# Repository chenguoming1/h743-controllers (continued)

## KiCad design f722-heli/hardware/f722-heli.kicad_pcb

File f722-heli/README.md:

# F722 controller: native0 routed milestone, work in progress

**Open [hardware/f722-heli.kicad_pro](hardware/f722-heli.kicad_pro). The selected board has zero opens, geometric DRC errors, DRC warnings, ERC findings and parity findings. It is a fully routed geometric WIP milestone; fresh conditional DC is now recorded in the evidence supplement; electrical-system acceptance and manufacturing/flight qualification remain pending.**

PCB SHA-256: `84229c571433bd72d410fb18d02cffa3a380c00a87fbe1270e3a73b63f8dd6cd`. The [native0 checkpoint](layout-revision/checkpoints/native0-rx-complete-v1-20261013/README.md) and [canonical provenance](hardware/CANONICAL-SOURCE.json) bind all 61 paired design files. Only the PCB differs from native1; all 60 non-PCB files are exact.

The cumulative native change removes 18 tracks and one via, adds 36 tracks and two vias, and moves U15, R34 and R35 through three measured cardinal transforms, preserving all pad-net mappings. It has 2,525 native objects and 331 drilled objects. The separate final GREEN cleanup removes two exact remnants. All required new physical gates and all 22 actual IO protection checks pass. Scoped cleanup reference applicability and residual RX crossing/MISO edge concerns are recorded in the checkpoint; geometry checks do not establish fast-edge or ESD equivalence.

The fresh selected-source DC result passes **294 required accessory/logic/USB cases on both grids**, 15 numerical comparisons and five VCAP copper loops. All 11 servo cases are illustrations. Six heavier current illustrations exceed the version-qualified Hobbywing V4.1 **10 A continuous BEC** reference even where ideal-source board-pad voltage passes. The raw aggregate remains false for the 18.56 A single-feed illustration, whose four servo pads fall below 6 V. This result does not qualify the servo system. The intended KST servos specify **6.0-8.4 V; raw 12.6 V servo operation is excluded**. The raw servo bus bypasses U5 electronics protection. V4.1's 30 A peak figure provides no installed duty-cycle qualification, and actual ESC/servo revisions, mating contacts and harness limits remain unbound. See the [power scope correction](layout-revision/checkpoints/native0-rx-complete-v1-20261013/evidence/power/POWER-SCOPE-CORRECTION.md).

The conditional 27 MHz prototype/bench limits, flash settling, BARO/IMU noise and ESD/EMC checks remain. The approved requested 400 kHz I2C setup remains unapplied; it can produce an actual bus clock above 400 kHz under the reviewed timing assumptions. The 385 kHz refinement remains unapproved and unapplied. Both new signal vias retain exact tenting/mask and actual pad/paste/metal-clearance evidence, including GREEN in the flash package region. JLC filled/capped-process applicability, ordinary-via process/stack, USB slots and panel acceptance remain unresolved. No process or firmware change is made here.

Saved-board restoration from the public native1 source is tested byte-for-byte. The compact cumulative transaction data and original two-stage native evidence are preserved; a full portable native-proof replay is not claimed. No heavy native, geometry or solver workload was repeated for packaging. The [conditional DC and local assembly supplement](layout-revision/checkpoints/native0-rx-complete-v1-20261013/supplements/conditional-dc-v1/README.md) records fresh native0 evidence and complete reduced results. The full raw field archive remains local with exact hashes; portable heavy replay is unrun. The nominal moved-part review passes while factory process acceptance remains open. Native1 results remain historical.

The [static firmware mapping receipt](layout-revision/checkpoints/native0-rx-complete-v1-20261013/supplements/conditional-dc-v1/firmware/REVIEW.md) passes 29 mapping rows and enumerates all 31 target resources, including shared PPM/SBUS and unused TX1. Installed binary, boot/DFU, IMU axes and physical runtime remain unverified.

The [static IMU and internal CAM supplement](layout-revision/checkpoints/native0-rx-complete-v1-20261013/supplements/imu-cam-v1/README.md) records the A/B-edge-forward orientation, actual INTERNAL WIP outputs, the drill-comparison tool correction and preserved U15 mask-contour differences. [Remaining decisions and acceptance gates](layout-revision/checkpoints/native0-rx-complete-v1-20261013/supplements/imu-cam-v1/OUTSTANDING-GATES.md) separate system choices, factory acceptance and prototype tests.

## Historical manufacturing records

Older docs/, validation/, manufacturing/ exports and [final95 status](README-final95-historical.md) describe earlier geometry. Regenerate final assembly outputs from the eventual released board and verify factory orientation. Selected R35 is at (29.2,23.9), B.Cu, 180 degrees; the historical native1 270-degree note is inapplicable. U15 and R34 also use their selected measured poses. All prior checkpoints and B-RID files remain unchanged. See [layout history](layout-revision/README.md). No fabrication or flight release is made here.

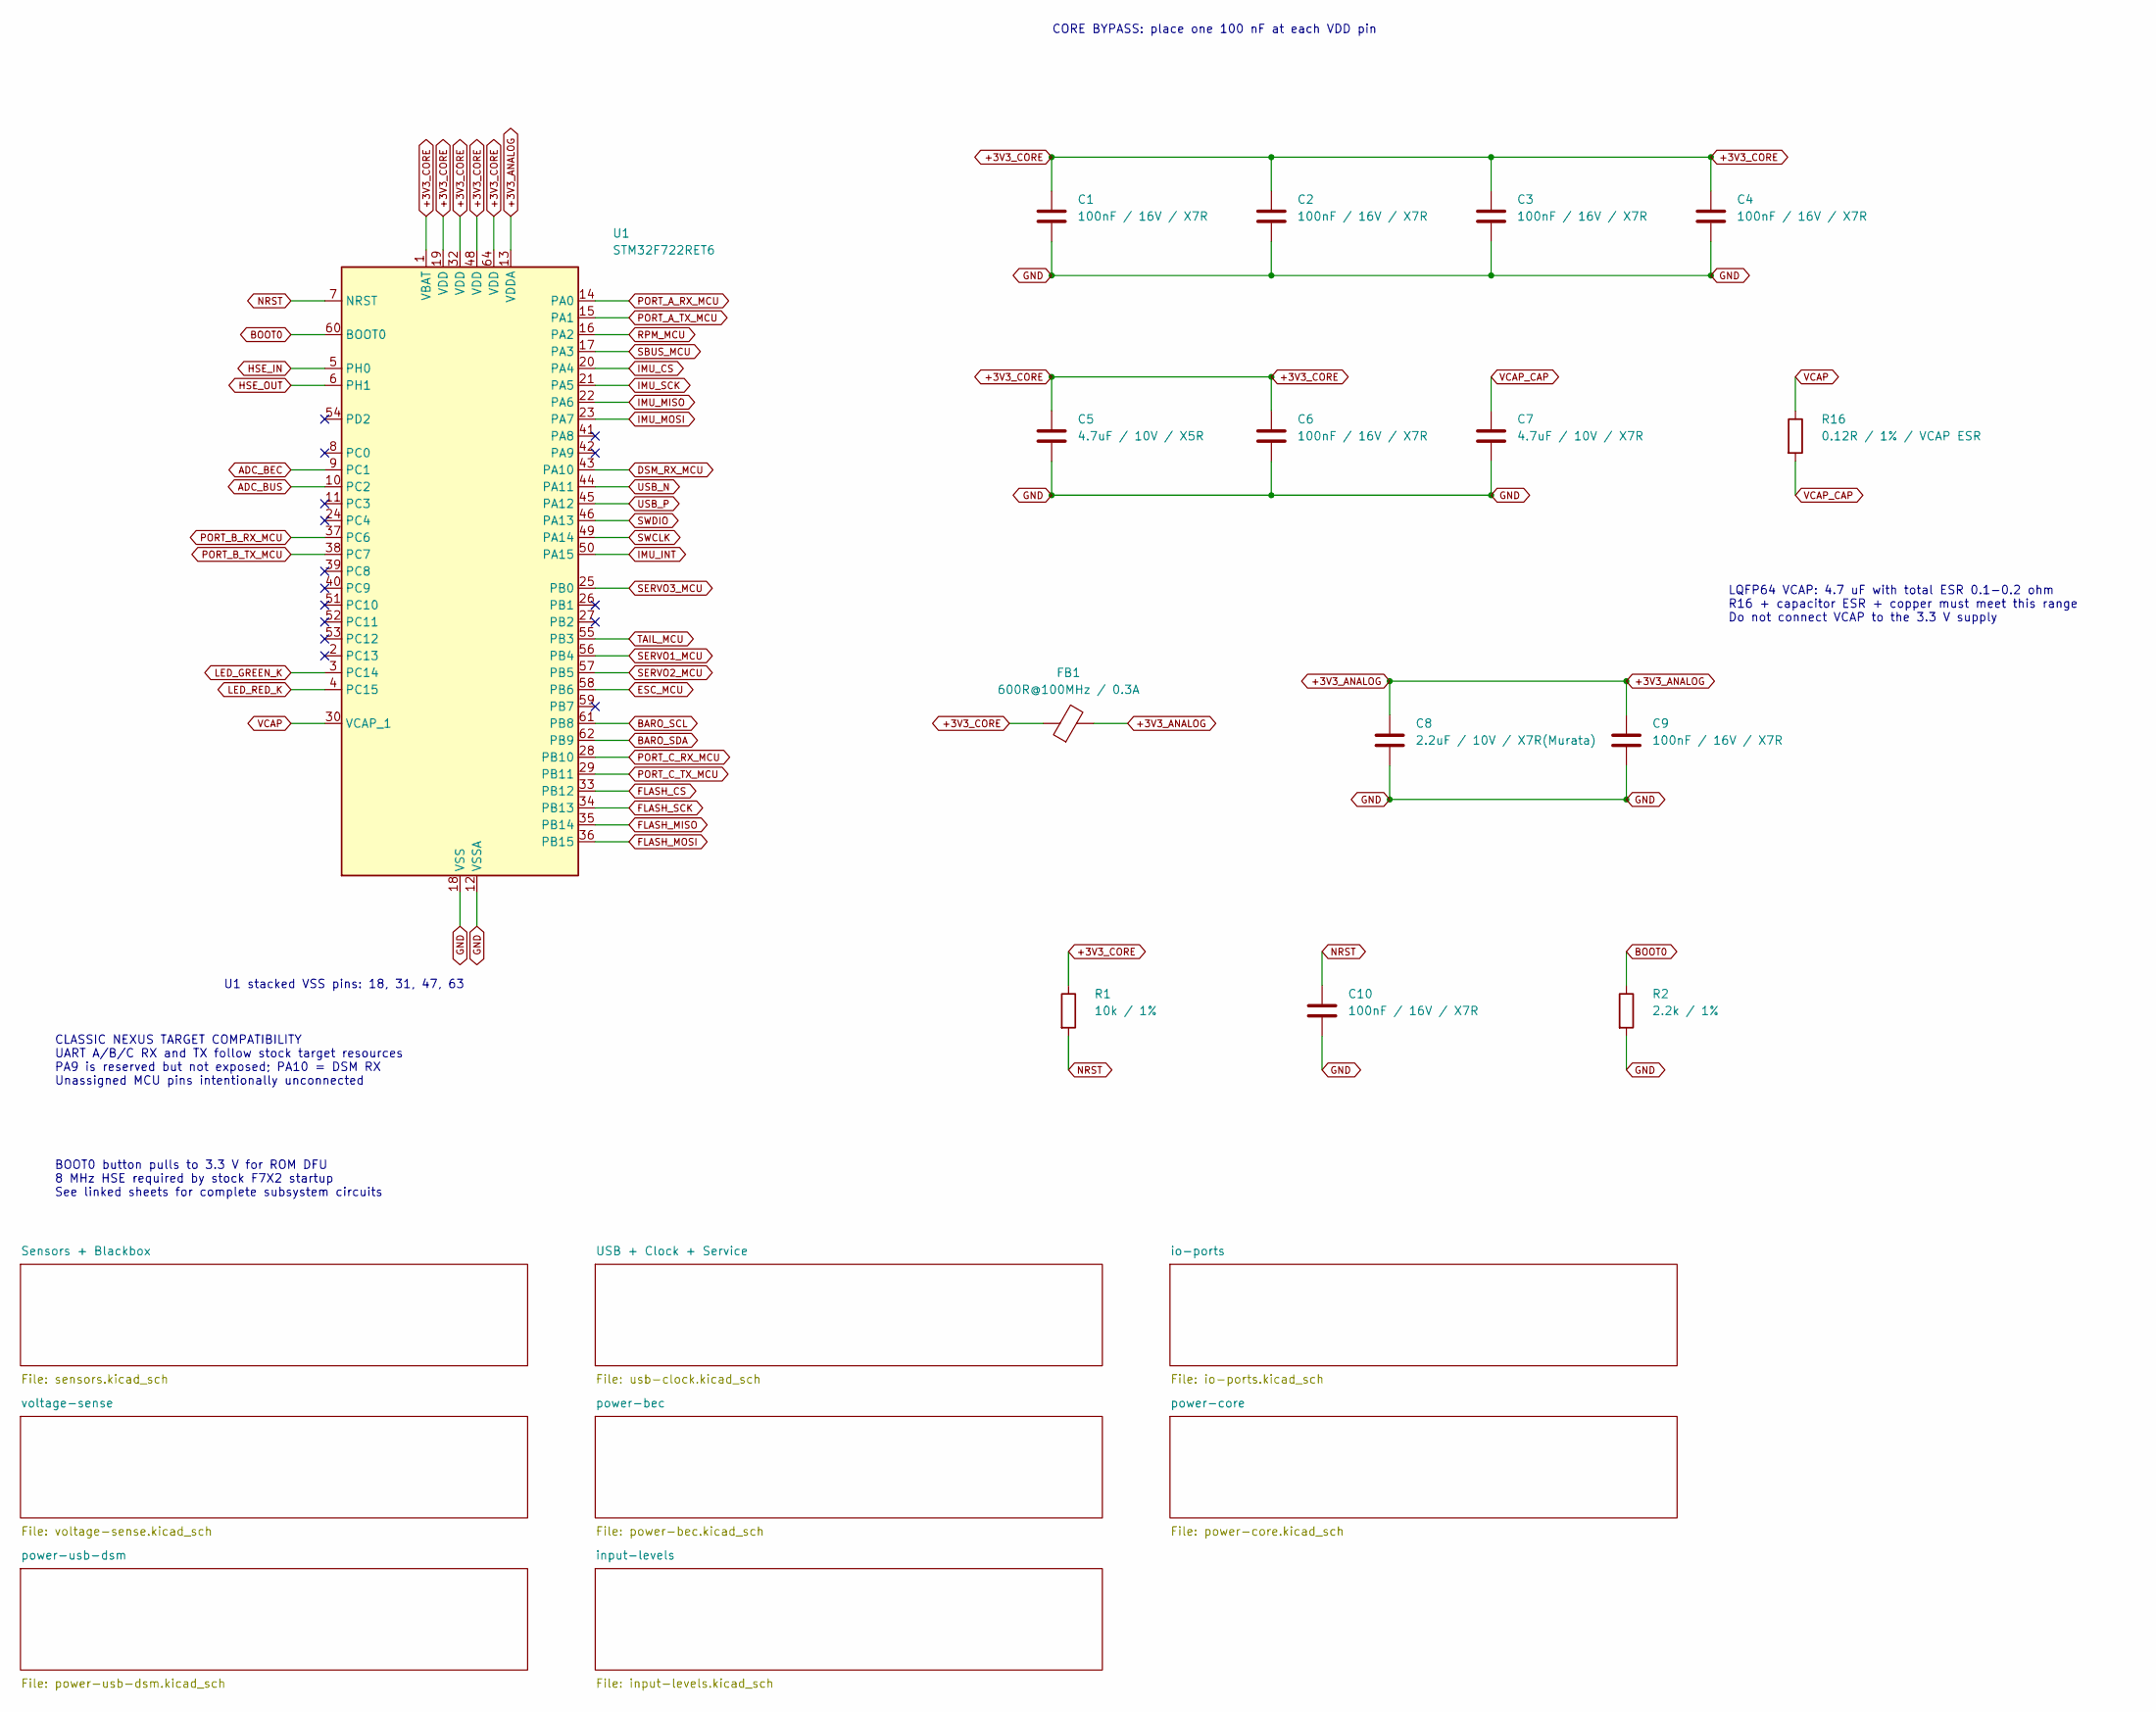
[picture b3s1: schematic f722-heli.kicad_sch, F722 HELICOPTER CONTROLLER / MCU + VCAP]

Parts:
C1, C2, C3, C4, C6, C9, C10: 100nF / 16V / X7R; C_0402_1005Metric; MPN CL05B104KO5NNNC; LCSC C1525
C5: 4.7uF / 10V / X5R; C_0603_1608Metric; MPN CL10A475KP8NNNC; LCSC C1705
C7: 4.7uF / 10V / X7R; C_0603_1608Metric; MPN GRM188Z71A475KE15D; LCSC C913474
C8: 2.2uF / 10V / X7R(Murata); Murata_GRM155Z71A225KE44_0402; MPN GRM155Z71A225KE44D; LCSC C2999759
FB1: 600R@100MHz / 0.3A; Murata_BLM15AG_0402; MPN BLM15AG601SN1D; LCSC C76884
R1: 10k / 1%; R_0402_1005Metric; MPN 0402WGF1002TCE; LCSC C25744
R2: 2.2k / 1%; R_0402_1005Metric; MPN 0402WGF2201TCE; LCSC C25879
R16: 0.12R / 1% / VCAP ESR; R_Panasonic_ERJ3R_0603; MPN ERJ3RSFR12V; LCSC C4059772
U1: STM32F722RET6; LQFP-64_10x10mm_P0.5mm; MPN STM32F722RET6; LCSC C118207

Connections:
+3V3_ANALOG: C8.1, C9.1, FB1.2, U1.13 (VDDA)
+3V3_CORE: C1.1, C2.1, C3.1, C4.1, C5.1, C6.1, FB1.1, R1.1, U1.1 (VBAT), U1.19 (VDD), U1.32 (VDD), U1.48 (VDD), U1.64 (VDD); also elsewhere on the board
ADC_BEC: U1.9 (PC1); also elsewhere on the board
ADC_BUS: U1.10 (PC2); also elsewhere on the board
BARO_SCL: U1.61 (PB8); also elsewhere on the board
BARO_SDA: U1.62 (PB9); also elsewhere on the board
BOOT0: R2.1, U1.60 (BOOT0); also elsewhere on the board
DSM_RX_MCU: U1.43 (PA10); also elsewhere on the board
FLASH_CS: U1.33 (PB12); also elsewhere on the board
FLASH_MISO: U1.35 (PB14); also elsewhere on the board
FLASH_MOSI: U1.36 (PB15); also elsewhere on the board
FLASH_SCK: U1.34 (PB13); also elsewhere on the board
GND: C1.2, C2.2, C3.2, C4.2, C5.2, C6.2, C7.2, C8.2, C9.2, C10.2, R2.2, U1.12 (VSSA), U1.18 (VSS), U1.31 (VSS), U1.47 (VSS), U1.63 (VSS); also elsewhere on the board
HSE_IN: U1.5 (PH0); also elsewhere on the board
HSE_OUT: U1.6 (PH1); also elsewhere on the board
IMU_CS: U1.20 (PA4); also elsewhere on the board
IMU_INT: U1.50 (PA15); also elsewhere on the board
IMU_MISO: U1.22 (PA6); also elsewhere on the board
IMU_MOSI: U1.23 (PA7); also elsewhere on the board
IMU_SCK: U1.21 (PA5); also elsewhere on the board
LED_GREEN_K: U1.3 (PC14); also elsewhere on the board
LED_RED_K: U1.4 (PC15); also elsewhere on the board
NRST: C10.1, R1.2, U1.7 (NRST); also elsewhere on the board
PORT_A_RX_MCU: U1.14 (PA0); also elsewhere on the board
PORT_A_TX_MCU: U1.15 (PA1); also elsewhere on the board
PORT_B_RX_MCU: U1.37 (PC6); also elsewhere on the board
PORT_B_TX_MCU: U1.38 (PC7); also elsewhere on the board
PORT_C_RX_MCU: U1.28 (PB10); also elsewhere on the board
PORT_C_TX_MCU: U1.29 (PB11); also elsewhere on the board
SERVO1_MCU: U1.56 (PB4); also elsewhere on the board
SERVO2_MCU: U1.57 (PB5); also elsewhere on the board
SERVO3_MCU: U1.25 (PB0); also elsewhere on the board
SWCLK: U1.49 (PA14); also elsewhere on the board
SWDIO: U1.46 (PA13); also elsewhere on the board
TAIL_MCU: U1.55 (PB3); also elsewhere on the board
USB_N: U1.44 (PA11); also elsewhere on the board
USB_P: U1.45 (PA12); also elsewhere on the board
VCAP: R16.1, U1.30 (VCAP_1)
VCAP_CAP: C7.1, R16.2

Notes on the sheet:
CLASSIC NEXUS TARGET COMPATIBILITY UART A/B/C RX and TX follow stock target resources PA9 is reserved but not exposed; PA10 = DSM RX Unassigned MCU pins intentionally unconnected
CORE BYPASS: place one 100 nF at each VDD pin
LQFP64 VCAP: 4.7 uF with total ESR 0.1-0.2 ohm R16 + capacitor ESR + copper must meet this range Do not connect VCAP to the 3.3 V supply
BOOT0 button pulls to 3.3 V for ROM DFU 8 MHz HSE required by stock F7X2 startup See linked sheets for complete subsystem circuits
U1 stacked VSS pins: 18, 31, 47, 63

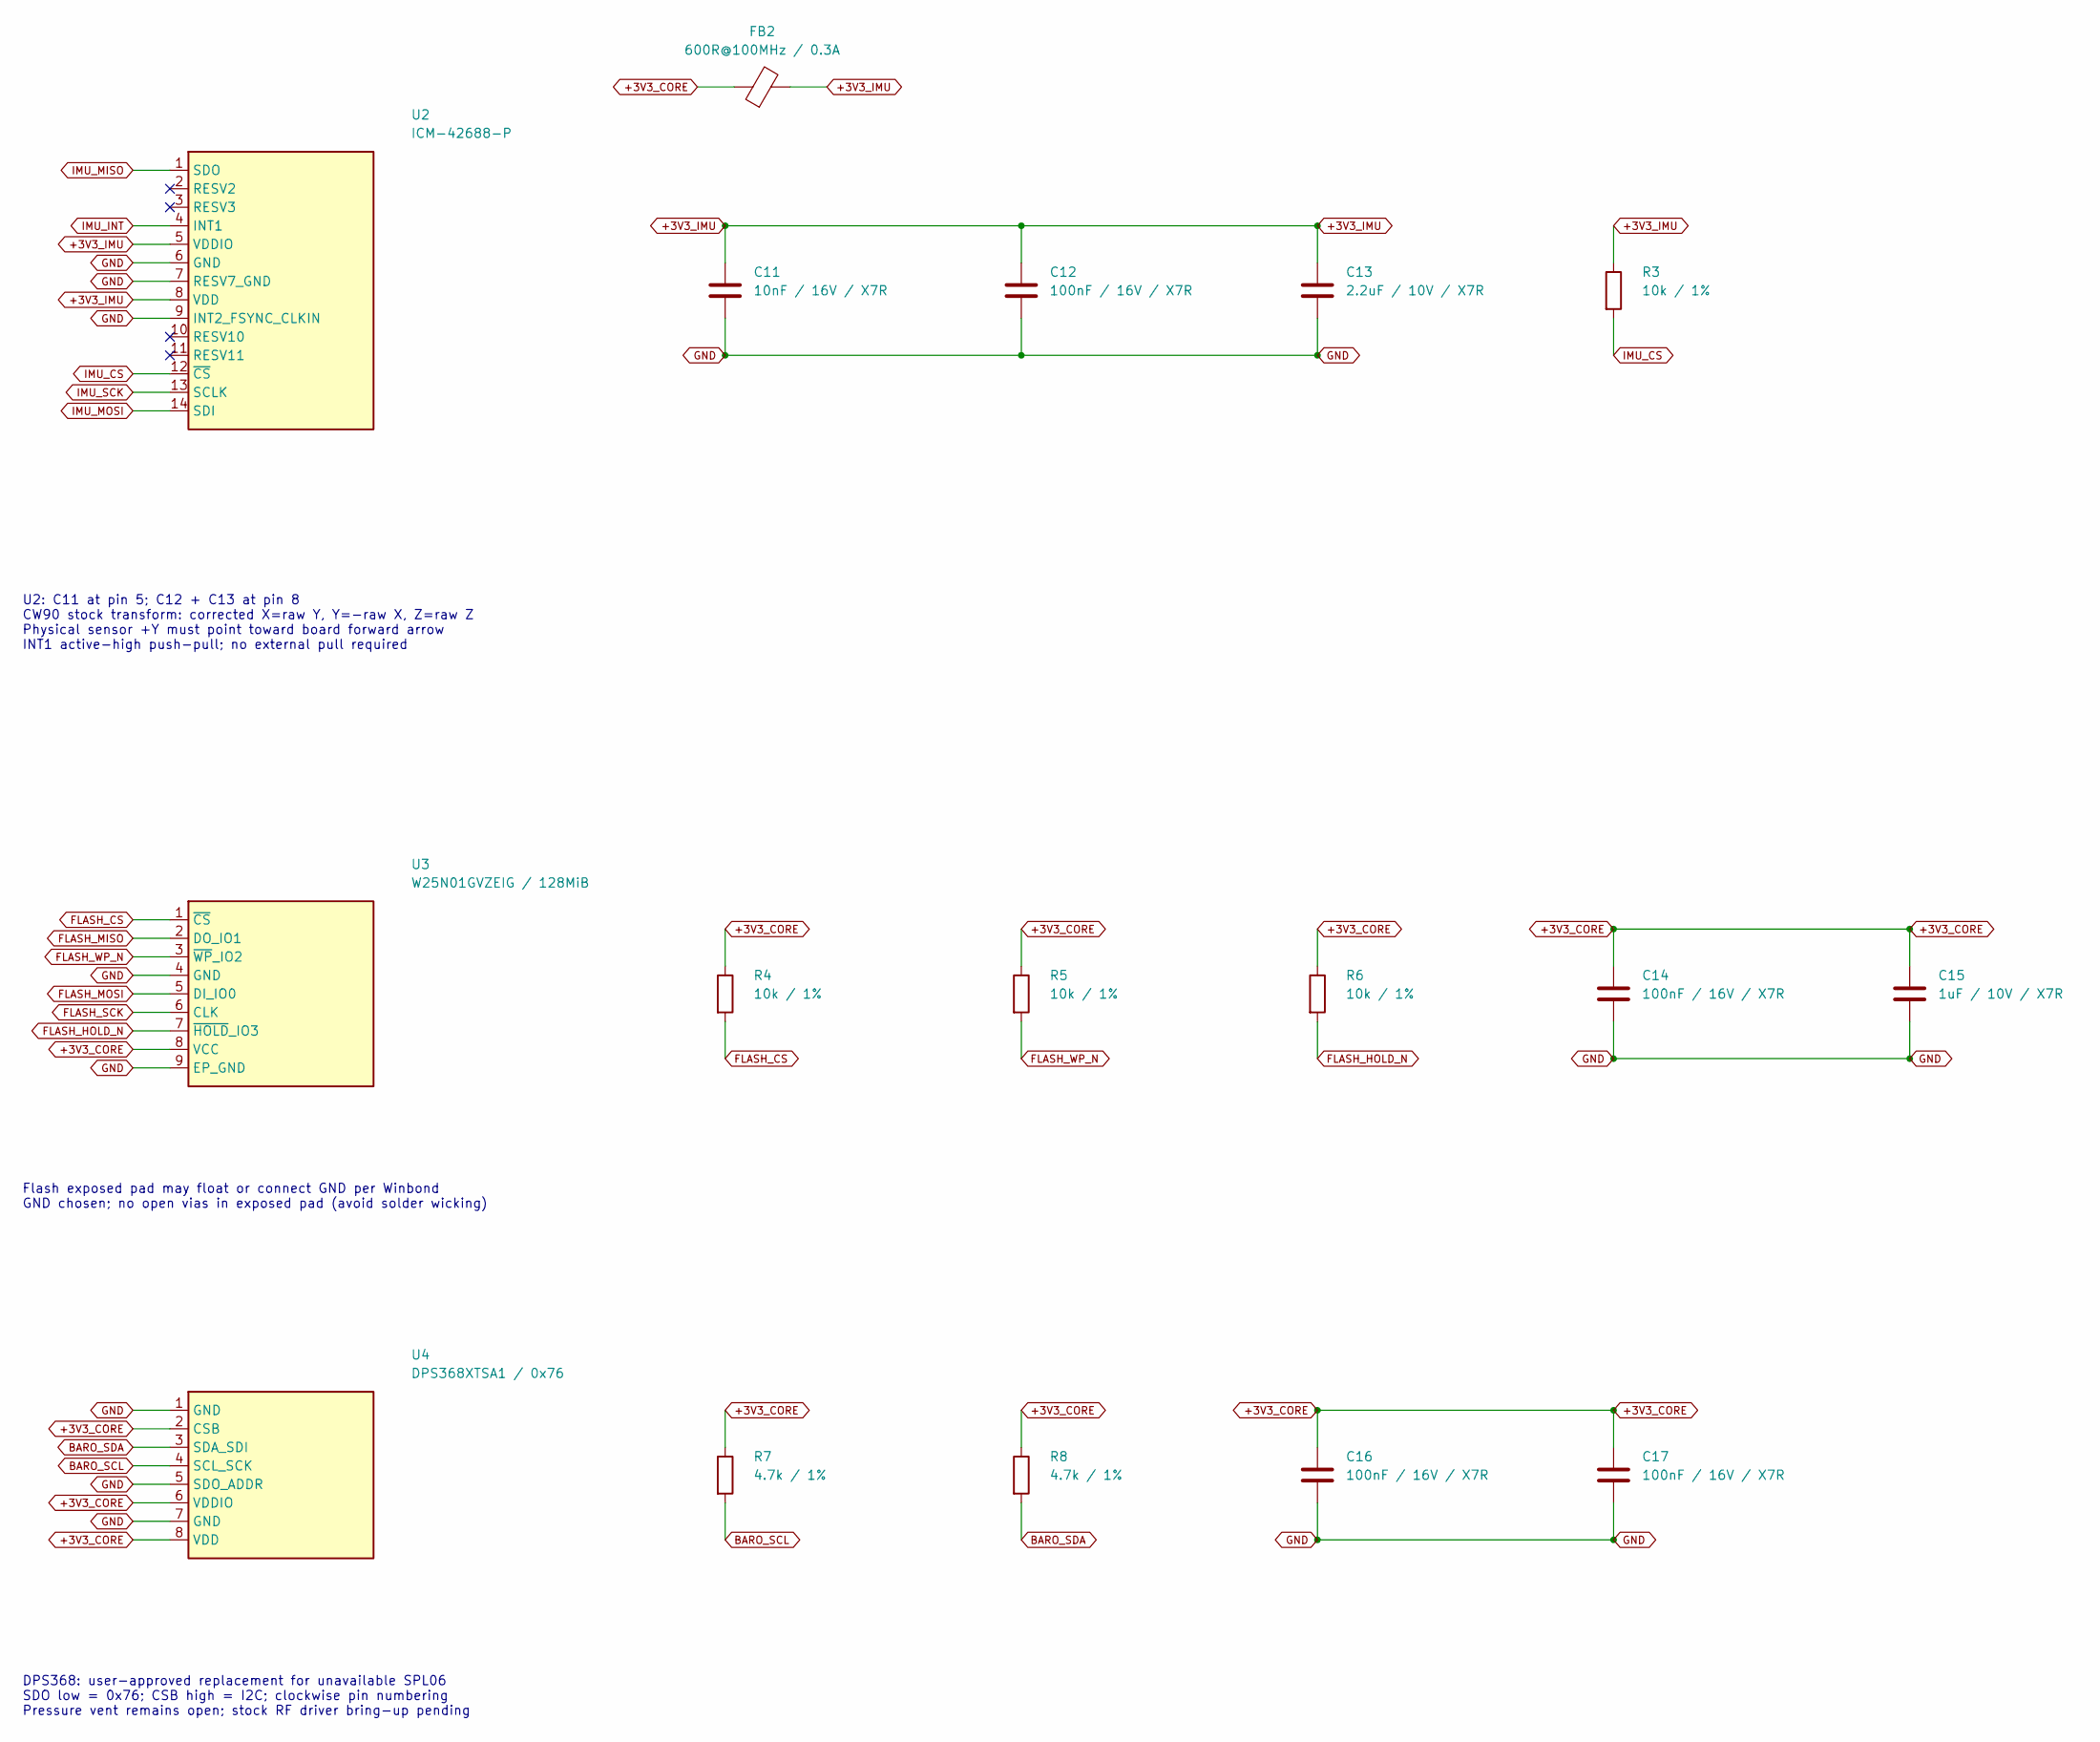
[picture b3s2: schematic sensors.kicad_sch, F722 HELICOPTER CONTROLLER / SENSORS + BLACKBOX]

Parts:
C11: 10nF / 16V / X7R; C_0402_1005Metric; MPN CL05B103KO5NNNC; LCSC C318577
C12, C14, C16, C17: 100nF / 16V / X7R; C_0402_1005Metric; MPN CL05B104KO5NNNC; LCSC C1525
C13: 2.2uF / 10V / X7R; C_0603_1608Metric; MPN CL10B225KP8NNNC; LCSC C100082
C15: 1uF / 10V / X7R; C_0603_1608Metric; MPN CL10B105KP8NNNC; LCSC C95843
FB2: 600R@100MHz / 0.3A; Murata_BLM15AG_0402; MPN BLM15AG601SN1D; LCSC C76884
R3, R4, R6: 10k / 1%; R_0402_1005Metric; MPN 0402WGF1002TCE; LCSC C25744
R5: 10k / 1%; R_0402_1005Metric_R5_ClearPin1Silk; MPN 0402WGF1002TCE; LCSC C25744
R7, R8: 4.7k / 1%; R_0402_1005Metric; MPN 0402WGF4701TCE; LCSC C25900
U2: ICM-42688-P; LGA-14_3x2.5mm_P0.5mm_LayoutBorder3x4y; MPN ICM-42688-P; LCSC C1850418
U3: W25N01GVZEIG / 128MiB; WSON-8-1EP_8x6mm_P1.27mm_EP3.4x4.3mm; MPN W25N01GVZEIG; LCSC C88868
U4: DPS368XTSA1 / 0x76; Infineon_DPS368_VLGA-8_2.5x2mm_SMD; MPN DPS368XTSA1; LCSC C3232508

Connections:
+3V3_CORE: C14.1, C15.1, C16.1, C17.1, FB2.1, R4.1, R5.1, R6.1, R7.1, R8.1, U3.8 (VCC), U4.2 (CSB), U4.6 (VDDIO), U4.8 (VDD); also elsewhere on the board
+3V3_IMU: C11.1, C12.1, C13.1, FB2.2, R3.1, U2.5 (VDDIO), U2.8 (VDD)
BARO_SCL: R7.2, U4.4 (SCL_SCK); also elsewhere on the board
BARO_SDA: R8.2, U4.3 (SDA_SDI); also elsewhere on the board
FLASH_CS: R4.2, U3.1 (~CS); also elsewhere on the board
FLASH_HOLD_N: R6.2, U3.7 (~HOLD_IO3)
FLASH_MISO: U3.2 (DO_IO1); also elsewhere on the board
FLASH_MOSI: U3.5 (DI_IO0); also elsewhere on the board
FLASH_SCK: U3.6 (CLK); also elsewhere on the board
FLASH_WP_N: R5.2, U3.3 (~WP_IO2)
GND: C11.2, C12.2, C13.2, C14.2, C15.2, C16.2, C17.2, U2.6 (GND), U2.7 (RESV7_GND), U2.9 (INT2_FSYNC_CLKIN), U3.4 (GND), U3.9 (EP_GND), U4.1 (GND), U4.5 (SDO_ADDR), U4.7 (GND); also elsewhere on the board
IMU_CS: R3.2, U2.12 (~CS); also elsewhere on the board
IMU_INT: U2.4 (INT1); also elsewhere on the board
IMU_MISO: U2.1 (SDO); also elsewhere on the board
IMU_MOSI: U2.14 (SDI); also elsewhere on the board
IMU_SCK: U2.13 (SCLK); also elsewhere on the board

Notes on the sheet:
U2: C11 at pin 5; C12 + C13 at pin 8 CW90 stock transform: corrected X=raw Y, Y=-raw X, Z=raw Z Physical sensor +Y must point toward board forward arrow INT1 active-high push-pull; no external pull required
Flash exposed pad may float or connect GND per Winbond GND chosen; no open vias in exposed pad (avoid solder wicking)
DPS368: user-approved replacement for unavailable SPL06 SDO low = 0x76; CSB high = I2C; clockwise pin numbering Pressure vent remains open; stock RF driver bring-up pending

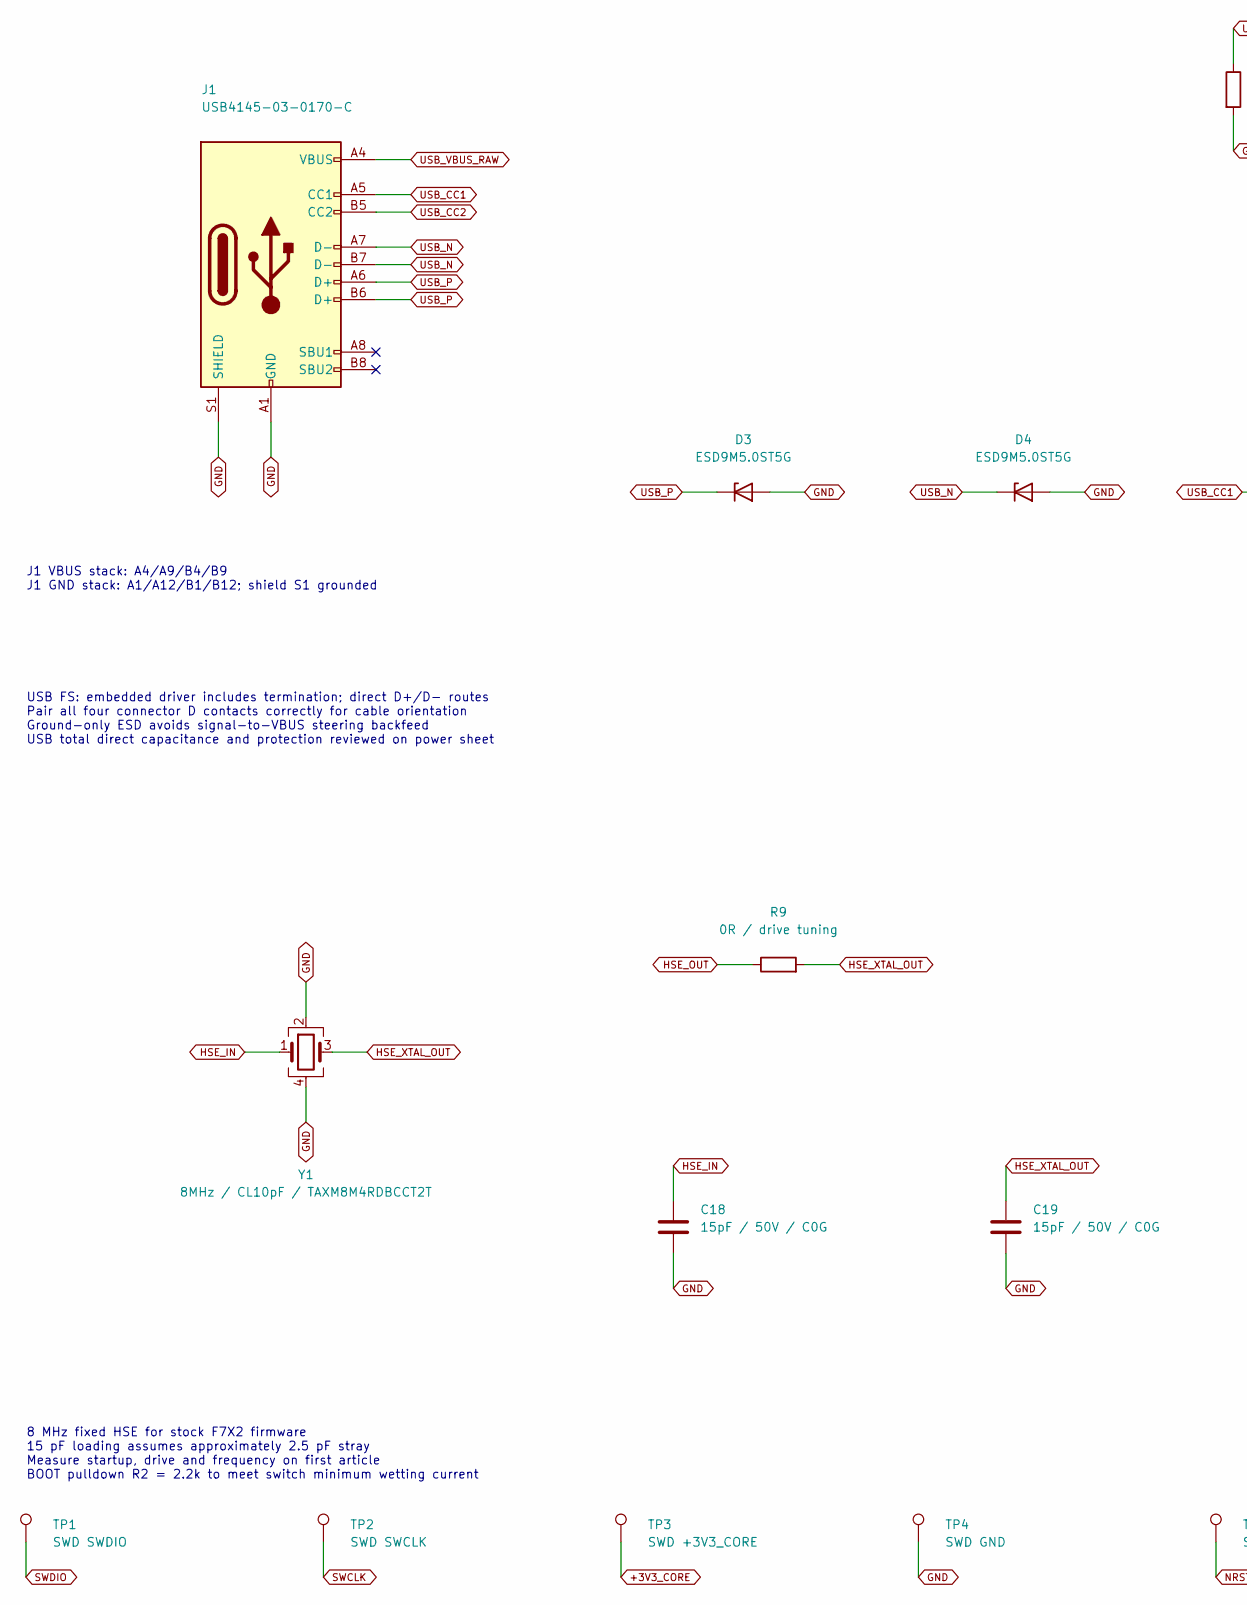
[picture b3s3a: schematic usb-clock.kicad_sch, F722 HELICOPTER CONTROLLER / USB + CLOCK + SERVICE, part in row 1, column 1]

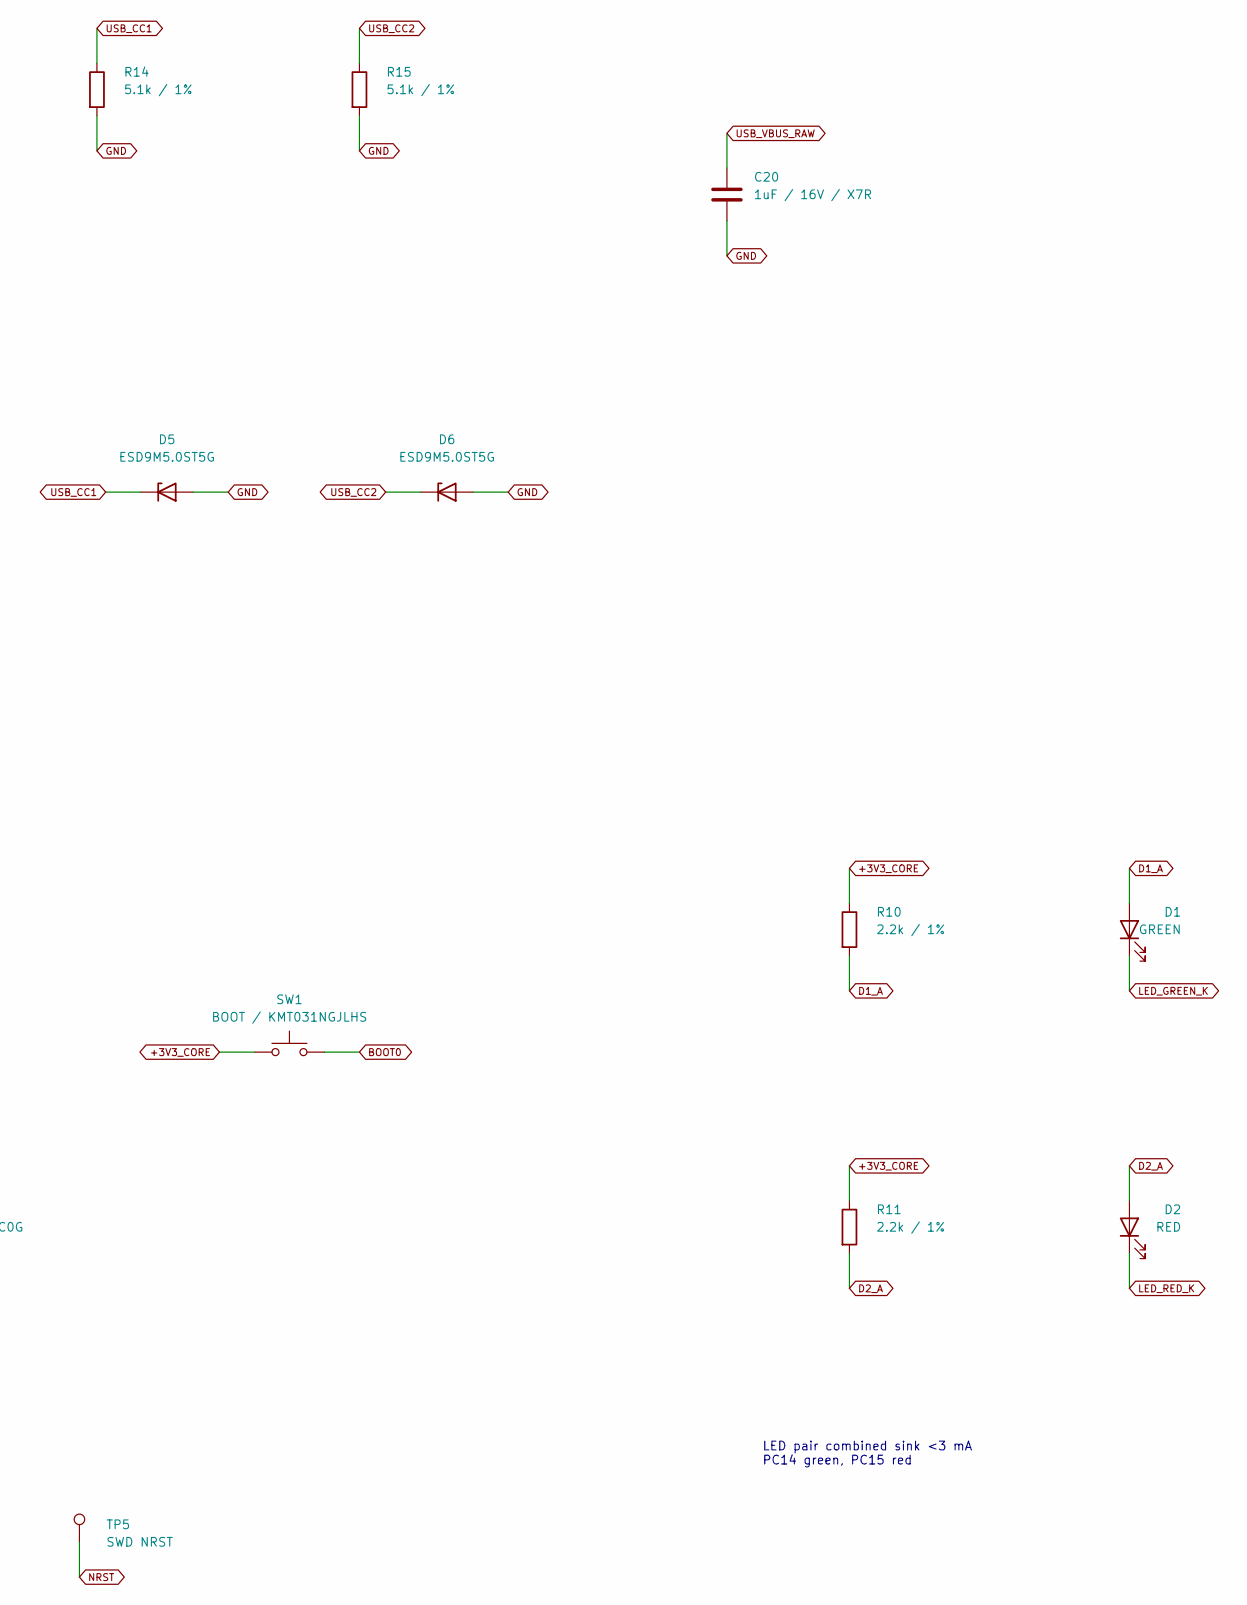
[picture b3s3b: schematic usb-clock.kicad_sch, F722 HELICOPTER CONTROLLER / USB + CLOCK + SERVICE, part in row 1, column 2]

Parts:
C18, C19: 15pF / 50V / C0G; C_0402_1005Metric; MPN CL05C150JB5NNNC; LCSC C86285
C20: 1uF / 16V / X7R; C_0603_1608Metric; MPN CL10B105KO8NNNC; LCSC C59782
D1: GREEN; LED_0603_1608Metric; MPN KT-0603YG; LCSC C2289
D2: RED; LED_0603_1608Metric; MPN KT-0603R; LCSC C2286
D3, D4, D5, D6: ESD9M5.0ST5G; D_SOD-923; MPN ESD9M5.0ST5G; LCSC C242267
J1: USB4145-03-0170-C; USB_C_Receptacle_GCT_USB4145-03-0170-C_16P_Vertical; MPN USB4145-03-0170-C; LCSC C5181332
R9: 0R / drive tuning; R_0402_1005Metric; MPN 0402WGF0000TCE; LCSC C17168
R10, R11: 2.2k / 1%; R_0402_1005Metric; MPN 0402WGF2201TCE; LCSC C25879
R14, R15: 5.1k / 1%; R_0402_1005Metric; MPN 0402WGF5101TCE; LCSC C25905
SW1: BOOT / KMT031NGJLHS; CK_KMT031NGJLHS; MPN KMT031NGJLHS; LCSC C221708
TP1: SWD SWDIO; TestPoint_Pad_D1.0mm_Compact
TP2: SWD SWCLK; TestPoint_Pad_D1.0mm_Compact
TP3: SWD +3V3_CORE; TestPoint_Pad_D1.0mm_Compact
TP4: SWD GND; TestPoint_Pad_D1.0mm_Compact
TP5: SWD NRST; TestPoint_Pad_D1.0mm_Compact
Y1: 8MHz / CL10pF / TAXM8M4RDBCCT2T; Crystal_SMD_3225-4Pin_3.2x2.5mm; MPN TAXM8M4RDBCCT2T; LCSC C400090

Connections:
+3V3_CORE: R10.1, R11.1, SW1.1, TP3.1; also elsewhere on the board
BOOT0: SW1.2; also elsewhere on the board
D1_A: D1.2 (A), R10.2
D2_A: D2.2 (A), R11.2
GND: C18.2, C19.2, C20.2, D3.2 (A), D4.2 (A), D5.2 (A), D6.2 (A), J1.A1 (GND), J1.A12 (GND), J1.B1 (GND), J1.B12 (GND), J1.S1 (SHIELD), R14.2, R15.2, TP4.1, Y1.2, Y1.4; also elsewhere on the board
HSE_IN: C18.1, Y1.1; also elsewhere on the board
HSE_OUT: R9.1; also elsewhere on the board
HSE_XTAL_OUT: C19.1, R9.2, Y1.3
LED_GREEN_K: D1.1 (K); also elsewhere on the board
LED_RED_K: D2.1 (K); also elsewhere on the board
NRST: TP5.1; also elsewhere on the board
SWCLK: TP2.1; also elsewhere on the board
SWDIO: TP1.1; also elsewhere on the board
USB_CC1: D5.1 (K), J1.A5 (CC1), R14.1
USB_CC2: D6.1 (K), J1.B5 (CC2), R15.1
USB_N: D4.1 (K), J1.A7 (D-), J1.B7 (D-); also elsewhere on the board
USB_P: D3.1 (K), J1.A6 (D+), J1.B6 (D+); also elsewhere on the board
USB_VBUS_RAW: C20.1, J1.A4 (VBUS), J1.A9 (VBUS), J1.B4 (VBUS), J1.B9 (VBUS); also elsewhere on the board

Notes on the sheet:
USB FS: embedded driver includes termination; direct D+/D- routes Pair all four connector D contacts correctly for cable orientation Ground-only ESD avoids signal-to-VBUS steering backfeed USB total direct capacitance and protection reviewed on power sheet
8 MHz fixed HSE for stock F7X2 firmware 15 pF loading assumes approximately 2.5 pF stray Measure startup, drive and frequency on first article BOOT pulldown R2 = 2.2k to meet switch minimum wetting current
LED pair combined sink <3 mA PC14 green, PC15 red
J1 VBUS stack: A4/A9/B4/B9 J1 GND stack: A1/A12/B1/B12; shield S1 grounded
